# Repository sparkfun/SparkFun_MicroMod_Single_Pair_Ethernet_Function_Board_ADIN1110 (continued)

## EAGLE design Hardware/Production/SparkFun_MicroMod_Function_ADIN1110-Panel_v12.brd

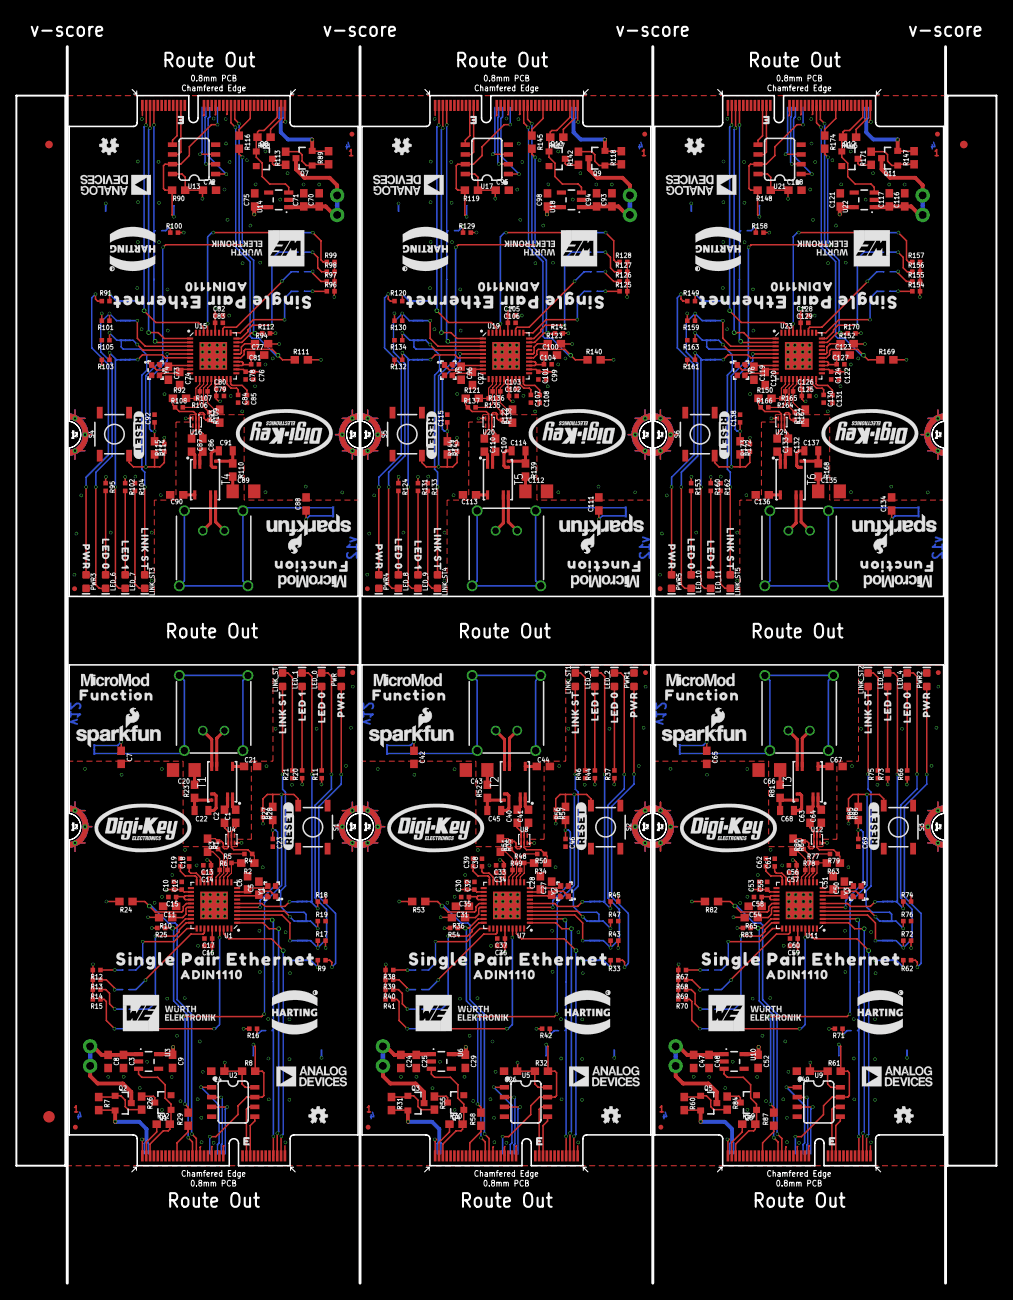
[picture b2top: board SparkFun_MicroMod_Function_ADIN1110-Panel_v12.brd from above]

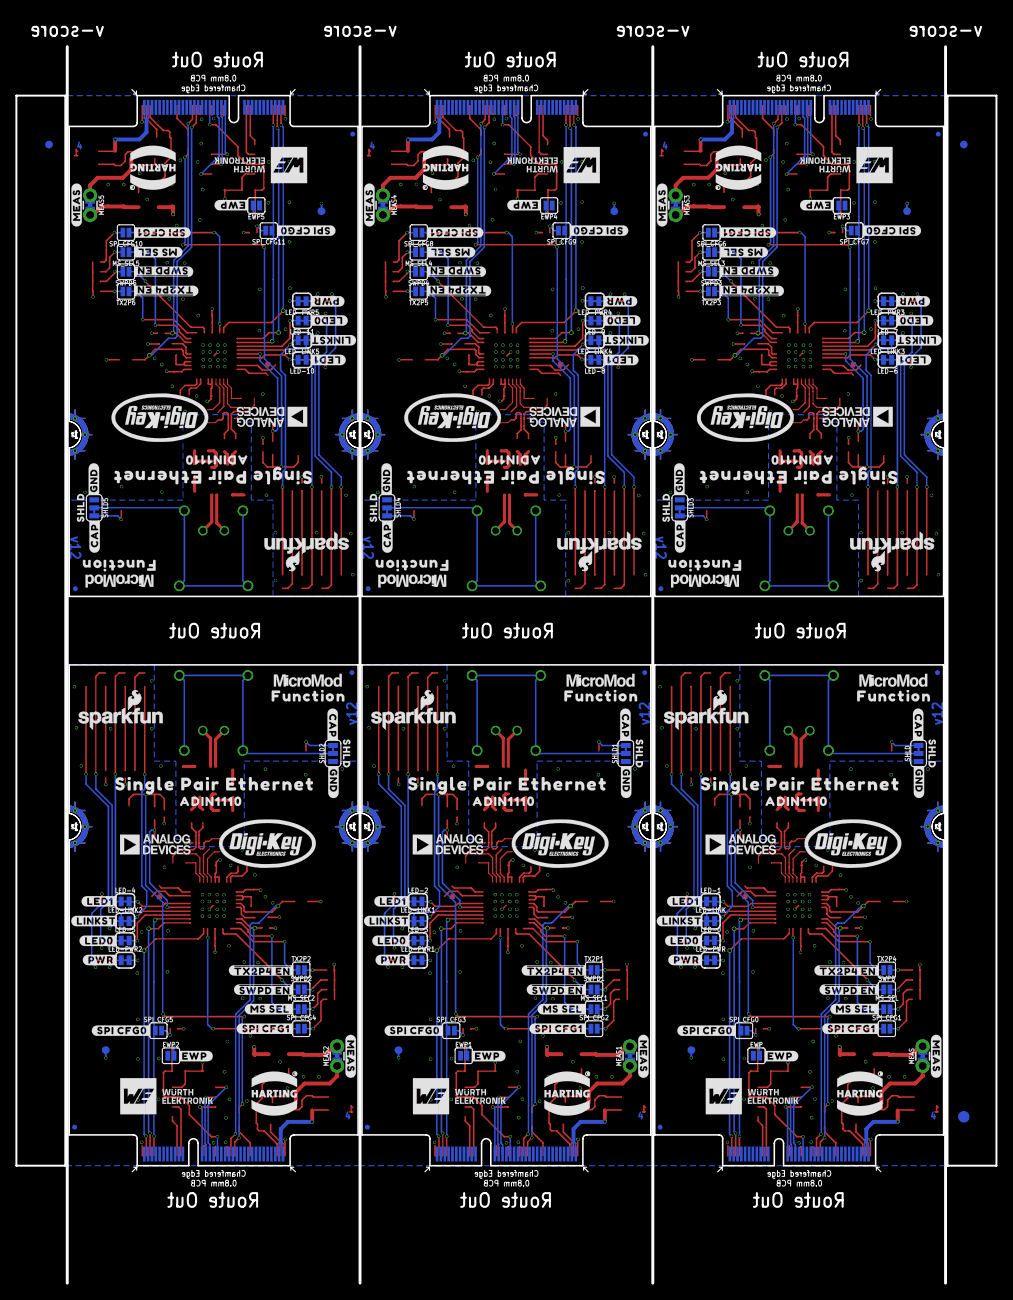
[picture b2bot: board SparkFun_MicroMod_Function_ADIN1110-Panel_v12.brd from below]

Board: 4 copper layers, 127.1 x 164.3 mm, 768 parts (231 on the bottom side), 390 nets.

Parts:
C1, C2, C40, C41, C63, C64, C86, C87, C109, C110, C132, C133: 0.22uF; 0603
C3, C4, C25, C26, C48, C49, C71, C72, C94, C95, C117, C118: 0.1uF; 0603
C5, C6, C27, C28, C50, C51, C73, C74, C96, C97, C119, C120: 10pF; 0603
C7, C42, C65, C88, C111, C134: 3.3nF; 0603
C8, C9, C24, C29, C47, C52, C70, C75, C93, C98, C116, C121: 1.0uF; 0603
C10, C13, C15, C16, C18, C23, C30, C33, C35, C36, C38, C46, C53, C56, C58, C59, C61, C69, C76, C79, C81, C82, C84, C92, C99, C102, C104, C105, C107, C115, C122, C125, C127, C128, C130, C138: 0.1uF; 0402-TIGHT
C11, C31, C54, C77, C100, C123: 0.68uF; 0603
C12, C14, C17, C32, C34, C37, C55, C57, C60, C78, C80, C83, C101, C103, C106, C124, C126, C129: 10nF; 0402-TIGHT
C19, C39, C62, C85, C108, C131: 1.0uF; 0402-TIGHT
C20, C43, C66, C89, C112, C135: 1.0nF/2kV; 1206
C21, C44, C67, C90, C113, C136: 0.1uF/50V; 0603
C22, C45, C68, C91, C114, C137: 470nF/100V; 0805
CIPO, CIPO1, CIPO2, CIPO3, CIPO4, CIPO5: TEST-POINTTP_15TH_THRU; TP_15TH
COPI, COPI1, COPI2, COPI3, COPI4, COPI5: TEST-POINTTP_15TH_THRU; TP_15TH
CS, CS1, CS2, CS3, CS4, CS5: TEST-POINTTP_15TH_THRU; TP_15TH
E$1, E$2, E$3, E$4: FIDUCIAL-1X2
E$5, E$6: FIDUCIAL-1.5X3
EWP, EWP1, EWP2, EWP3, EWP4, EWP5: JUMPER-SMT_2_NO_SILK; SMT-JUMPER_2_NO_SILK
FD1, FD2, FD3, FD4, FD5, FD6, FD7, FD8, FD9, FD10, FD11, FD12, FD13, FD14, FD15, FD16, FD17, FD18, FD19, FD20, FD21, FD22, FD23, FD24: FIDUCIALUFIDUCIAL; FIDUCIAL-MICRO
INT, INT1, INT2, INT3, INT4, INT5: TEST-POINTTP_15TH_THRU; TP_15TH
J1, J4, J6, J8, J10, J12: IP20(RJ50); T1_INDUSTRIAL_JACK_AH_IP20
J2, J3, J5, J7, J9, J11: MICROMOD_FUNCTION_STANDARD; M.2-CARD-E-22_FUNCTION_STANDARD
LED-0, LED-1, LED-2, LED-3, LED-4, LED-5, LED-6, LED-7, LED-8, LED-9, LED-10, LED-11: JUMPER-SMT_2_NC_TRACE_SILK; SMT-JUMPER_2_NC_TRACE_SILK
LED-LINK, LED-LINK1, LED-LINK2, LED-LINK3, LED-LINK4, LED-LINK5: JUMPER-SMT_2_NC_TRACE_SILK; SMT-JUMPER_2_NC_TRACE_SILK
LED-PWR, LED-PWR1, LED-PWR2, LED-PWR3, LED-PWR4, LED-PWR5: JUMPER-SMT_2_NC_TRACE_SILK; SMT-JUMPER_2_NC_TRACE_SILK
LED_0, LED_2, LED_4, LED_6, LED_8, LED_10: Green; LED-0603
LED_1, LED_3, LED_5, LED_7, LED_9, LED_11: Yellow; LED-0603
LINK_ST, LINK_ST1, LINK_ST2, LINK_ST3, LINK_ST4, LINK_ST5: Blue; LED-0603
LOGO1, LOGO4, LOGO6, LOGO8, LOGO10, LOGO12: SFE_LOGO_NAME_FLAME.1_INCH; SFE_LOGO_NAME_FLAME_.1
LOGO2, LOGO3, LOGO5, LOGO7, LOGO9, LOGO11: OSHW-LOGOMINI; OSHW-LOGO-MINI
MEAS, MEAS1, MEAS2, MEAS3, MEAS4, MEAS5: JUMPER-COMBO_2_NC_TRACE; COMBO-JUMPER_2_NC_TRACE
MS_SEL, MS_SEL1, MS_SEL2, MS_SEL3, MS_SEL4, MS_SEL5: SMT-JUMPER_2_NO_SILK
PWR, PWR1, PWR2, PWR3, PWR4, PWR5: Red; LED-0603
Q1, Q4, Q6, Q8, Q10, Q12: 220mA/50V/3.5Ω; SOT23-3
Q2, Q3, Q5, Q7, Q9, Q11: 20V/4.2A/52mΩ/1.4W; SOT23-3
R1, R2, R34, R35, R63, R64, R92, R93, R121, R122, R150, R151: 49.9; 0603
R3, R4, R50, R51, R79, R80, R108, R109, R137, R138, R166, R167: 5.1k; 0402-TIGHT
R5, R6, R48, R49, R77, R78, R106, R107, R135, R136, R164, R165: 10.2k; 0402-TIGHT
R7, R8, R22, R30, R31, R32, R59, R60, R61, R88, R89, R90, R117, R118, R119, R146, R147, R148: 10k; 0603
R9, R11, R20, R21, R33, R37, R44, R46, R62, R66, R73, R75, R91, R95, R102, R104, R120, R124, R131, R133, R149, R153, R160, R162: 1k; 0402-TIGHT
R10, R24, R36, R53, R65, R82, R94, R111, R123, R140, R152, R169: 1.5k; 0603
R12, R13, R14, R15, R16, R17, R18, R19, R25, R38, R39, R40, R41, R42, R43, R45, R47, R54, R67, R68, R69, R70, R71, R72, R74, R76, R83, R96, R97, R98, R99, R100, R101, R103, R105, R112, R125, R126, R127, R128, R129, R130, R132, R134, R141, R154, R155, R156, R157, R158, R159, R161, R163, R170: 4.7k; 0402-TIGHT
R23, R29, R52, R58, R81, R87, R110, R116, R139, R145, R168, R174: 100Ω; 0603
R26, R55, R84, R113, R142, R171: 100; 0603
R27, R56, R85, R114, R143, R172: 4.7k; 0603
R28, R57, R86, R115, R144, R173: 100k; 0402-TIGHT
S1, S2, S3, S4, S5, S6: RESET; TACTILE_SWITCH_SMD_5.2MM
SHLD, SHLD1, SHLD2, SHLD3, SHLD4, SHLD5: SMT-JUMPER_3_1-NC_TRACE_SILK
SPI, SPI1, SPI2, SPI3, SPI4, SPI5: TEST-POINTTP_15TH_THRU; TP_15TH
SPI_CFG0, SPI_CFG1, SPI_CFG2, SPI_CFG3, SPI_CFG4, SPI_CFG5, SPI_CFG6, SPI_CFG7, SPI_CFG8, SPI_CFG9, SPI_CFG10, SPI_CFG11: SMT-JUMPER_2_NO_SILK
SWPD, SWPD1, SWPD2, SWPD3, SWPD4, SWPD5: SMT-JUMPER_2_NO_SILK
T1, T2, T3, T4, T5, T6: WE-STST; WE_STST_TRANSFORMER_1:1_SMD_3.2X4.7MM_74930030
TP1, TP2, TP3, TP4, TP5, TP6: TEST-POINT3X4; PAD.03X.04
TX2P1, TX2P2, TX2P3, TX2P4, TX2P5, TX2P6: SMT-JUMPER_2_NO_SILK
U1, U7, U11, U15, U19, U23: ADIN1110; LFCSP-40
U2, U5, U9, U13, U17, U21: EEPROM; SO08
U3, U6, U10, U14, U18, U22: 3.3V; SOT23-5
U4, U8, U12, U16, U20, U24: WE-TVS; WE_TVS_1.0X1.2MM
U$1, U$42, U$79, U$115, U$151, U$187: #RESET#0
U$2, U$71, U$107, U$143, U$179, U$215: HARTING_LOGO; HARTING_LOGO_9MM
U$3, U$36, U$37, U$63, U$73, U$74, U$109, U$110, U$145, U$146, U$181, U$182: MICROMOD_LOGO_.35
U$4, U$21, U$41, U$47, U$78, U$84, U$114, U$120, U$150, U$156, U$186, U$192: ADIN11100
U$5, U$69, U$105, U$141, U$177, U$213: DIGIKEY_LOGO
U$6, U$55, U$92, U$128, U$164, U$200: #PWR#19
U$7, U$39, U$76, U$112, U$148, U$184: PWR0
U$8, U$43, U$80, U$116, U$152, U$188: SHLD11
U$9, U$54, U$91, U$127, U$163, U$199: #EWP#18
U$10, U$56, U$93, U$129, U$165, U$201: #LED0#20
U$11, U$52, U$89, U$125, U$161, U$197: #GND#16
U$12, U$53, U$90, U$126, U$162, U$198: #CAP#17
U$13, U$59, U$96, U$132, U$168, U$204: ##TX2P4_EN##4
U$14, U$44, U$81, U$117, U$153, U$189: #SPI_CFG1#0
U$15, U$45, U$82, U$118, U$154, U$190: #MS_SEL#2
U$16, U$46, U$83, U$119, U$155, U$191: #SPI_CFG0#0
U$17, U$18, U$61, U$62, U$98, U$99, U$134, U$135, U$170, U$171, U$206, U$207: SINGLE_PAIR_ETHERNET0
U$19, U$72, U$108, U$144, U$180, U$216: WURTH_LOGO; WURTH_LOGO_9MM
U$20, U$64, U$100, U$136, U$172, U$208: ANALOG_DEVICE_LOGO_9MM
U$22, U$60, U$97, U$133, U$169, U$205: ##SWPD_EN##4
U$23, U$49, U$86, U$122, U$158, U$194: LED_03
U$24, U$26, U$40, U$48, U$77, U$85, U$113, U$121, U$149, U$157, U$185, U$193: FUNCTION0
U$25, U$50, U$87, U$123, U$159, U$195: LED_14
U$27, U$51, U$88, U$124, U$160, U$196: LINK_ST15
U$28, U$38, U$75, U$111, U$147, U$183: #MEAS#3
U$29, U$57, U$94, U$130, U$166, U$202: #LED1#21
U$30, U$65, U$101, U$137, U$173, U$209: HARTING_LOGO_9MM
U$31, U$58, U$95, U$131, U$167, U$203: #LINKST#2
U$32, U$66, U$102, U$138, U$174, U$210: WURTH_LOGO_9MM
U$33, U$70, U$106, U$142, U$178, U$214: ANALOG_DEVICES_LOGO; ANALOG_DEVICE_LOGO_9MM
U$34, U$67, U$103, U$139, U$175, U$211: DIGIKEY_LOGO
U$35, U$68, U$104, U$140, U$176, U$212: SFE_LOGO_NAME_FLAME_.1
Y1, Y2, Y3, Y4, Y5, Y6: 25MHz; CRYSTAL-SMD-2.0X1.6MM-WE

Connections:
1.1V: C11.1, C15.1, U1.23, U1.24
1.1V1: C31.1, C35.1, U7.23, U7.24
1.1V2: C54.1, C58.1, U11.23, U11.24
1.1V3: C77.1, C81.1, U15.23, U15.24
1.1V4: C100.1, C104.1, U19.23, U19.24
1.1V5: C123.1, C127.1, U23.23, U23.24
3.3V: C4.1, C9.1, C10.1, C12.1, C13.1, C14.1, C16.1, C17.1, LED-PWR.2, R8.1, R10.2, R11.1, R12.2, R13.2, R14.2, R15.2, R16.2, R17.2, R18.2, R20.1, R24.2, R25.2, R28.2, TP1.1, U1.16, U1.17, U1.22, U1.35, U2.8, U3.5
3.3V1: C26.1, C29.1, C30.1, C32.1, C33.1, C34.1, C36.1, C37.1, LED-PWR1.2, R32.1, R36.2, R37.1, R38.2, R39.2, R40.2, R41.2, R42.2, R43.2, R44.1, R45.2, R53.2, R54.2, R57.2, TP2.1, U5.8, U6.5, U7.16, U7.17, U7.22, U7.35
3.3V2: C49.1, C52.1, C53.1, C55.1, C56.1, C57.1, C59.1, C60.1, LED-PWR2.2, R61.1, R65.2, R66.1, R67.2, R68.2, R69.2, R70.2, R71.2, R72.2, R73.1, R74.2, R82.2, R83.2, R86.2, TP3.1, U9.8, U10.5, U11.16, U11.17, U11.22, U11.35
3.3V3: C72.1, C75.1, C76.1, C78.1, C79.1, C80.1, C82.1, C83.1, LED-PWR3.2, R90.1, R94.2, R95.1, R96.2, R97.2, R98.2, R99.2, R100.2, R101.2, R102.1, R103.2, R111.2, R112.2, R115.2, TP4.1, U13.8, U14.5, U15.16, U15.17, U15.22, U15.35
3.3V4: C95.1, C98.1, C99.1, C101.1, C102.1, C103.1, C105.1, C106.1, LED-PWR4.2, R119.1, R123.2, R124.1, R125.2, R126.2, R127.2, R128.2, R129.2, R130.2, R131.1, R132.2, R140.2, R141.2, R144.2, TP5.1, U17.8, U18.5, U19.16, U19.17, U19.22, U19.35
3.3V5: C118.1, C121.1, C122.1, C124.1, C125.1, C126.1, C128.1, C129.1, LED-PWR5.2, R148.1, R152.2, R153.1, R154.2, R155.2, R156.2, R157.2, R158.2, R159.2, R160.1, R161.2, R169.2, R170.2, R173.2, TP6.1, U21.8, U22.5, U23.16, U23.17, U23.22, U23.35
3.3V_IN: J2.73, R22.1
3.3V_IN1: J3.73, R30.1
3.3V_IN2: J5.73, R59.1
3.3V_IN3: J7.73, R88.1
3.3V_IN4: J9.73, R117.1
3.3V_IN5: J11.73, R146.1
!CS!: CS.1, J2.49, R25.1, U1.29
!CS!1: CS1.1, J3.49, R54.1, U7.29
!CS!2: CS2.1, J5.49, R83.1, U11.29
!CS!3: CS3.1, J7.49, R112.1, U15.29
!CS!4: CS4.1, J9.49, R141.1, U19.29
!CS!5: CS5.1, J11.49, R170.1, U23.29
!INT!: INT.1, J2.47, R24.1, U1.25
!INT!1: INT1.1, J3.47, R53.1, U7.25
!INT!2: INT2.1, J5.47, R82.1, U11.25
!INT!3: INT3.1, J7.47, R111.1, U15.25
!INT!4: INT4.1, J9.47, R140.1, U19.25
!INT!5: INT5.1, J11.47, R169.1, U23.25
!RESET!: J2.57, R29.1
!RESET!1: J3.57, R58.1
!RESET!2: J5.57, R87.1
!RESET!3: J7.57, R116.1
!RESET!4: J9.57, R145.1
!RESET!5: J11.57, R174.1
!SWPD_EN!: SWPD.1, U1.33
!SWPD_EN!1: SWPD1.1, U7.33
!SWPD_EN!2: SWPD2.1, U11.33
!SWPD_EN!3: SWPD3.1, U15.33
!SWPD_EN!4: SWPD4.1, U19.33
!SWPD_EN!5: SWPD5.1, U23.33
!TX2P4_EN!: TX2P4.1, U1.31
!TX2P4_EN!1: TX2P1.1, U7.31
!TX2P4_EN!2: TX2P2.1, U11.31
!TX2P4_EN!3: TX2P3.1, U15.31
!TX2P4_EN!4: TX2P5.1, U19.31
!TX2P4_EN!5: TX2P6.1, U23.31
A0: J2.36, U2.1
A1: J2.34, U2.2
A2: J2.32, U2.3
A3: J3.36, U5.1
A4: J3.32, U5.3
A5: J3.34, U5.2
A6: J5.36, U9.1
A7: J5.32, U9.3
A8: J5.34, U9.2
A9: J7.36, U13.1
A10: J7.32, U13.3
A11: J7.34, U13.2
A12: J9.36, U17.1
A13: J9.32, U17.3
A14: J9.34, U17.2
A15: J11.36, U21.1
A16: J11.32, U21.3
A17: J11.34, U21.2
DA+: J1.1, T1.7
DA+1: J4.1, T2.7
DA+2: J6.1, T3.7
DA+3: J8.1, T4.7
DA+4: J10.1, T5.7
DA+5: J12.1, T6.7
DA-: J1.2, T1.6
DA-1: J4.2, T2.6
DA-2: J6.2, T3.6
DA-3: J8.2, T4.6
DA-4: J10.2, T5.6
DA-5: J12.2, T6.6
EWP: EWP.2, J2.40, R8.2, U2.7
EWP1: EWP1.2, J3.40, R32.2, U5.7
EWP2: EWP2.2, J5.40, R61.2, U9.7
EWP3: EWP3.2, J7.40, R90.2, U13.7
EWP4: EWP4.2, J9.40, R119.2, U17.7
EWP5: EWP5.2, J11.40, R148.2, U21.7
GND: C3.2, C4.2, C5.2, C6.2, C7.2, C8.2, C9.2, C10.2, C11.2, C12.2, C13.2, C14.2, C15.2, C16.2, C17.2, C18.2, C19.2, C20.2, C21.2, C23.2, EWP.1, J2.1, J2.2, J2.8, J2.33, J2.39, J2.45, J2.75, J2.GND1, J2.GND2, J2.GND3, J2.GND4, J2.GND5, J2.GND6, PWR.C, Q1.2, R19.2, R21.1, S1.1, SHLD.1, U1.EP, U2.4, U3.2, U4.3, Y1.2, Y1.4
GND1: C24.2, C25.2, C26.2, C27.2, C28.2, C29.2, C30.2, C31.2, C32.2, C33.2, C34.2, C35.2, C36.2, C37.2, C38.2, C39.2, C42.2, C43.2, C44.2, C46.2, EWP1.1, J3.1, J3.2, J3.8, J3.33, J3.39, J3.45, J3.75, J3.GND1, J3.GND2, J3.GND3, J3.GND4, J3.GND5, J3.GND6, PWR1.C, Q4.2, R46.1, R47.2, S2.1, SHLD1.1, U5.4, U6.2, U7.EP, U8.3, Y2.2, Y2.4
GND2: C47.2, C48.2, C49.2, C50.2, C51.2, C52.2, C53.2, C54.2, C55.2, C56.2, C57.2, C58.2, C59.2, C60.2, C61.2, C62.2, C65.2, C66.2, C67.2, C69.2, EWP2.1, J5.1, J5.2, J5.8, J5.33, J5.39, J5.45, J5.75, J5.GND1, J5.GND2, J5.GND3, J5.GND4, J5.GND5, J5.GND6, PWR2.C, Q6.2, R75.1, R76.2, S3.1, SHLD2.1, U9.4, U10.2, U11.EP, U12.3, Y3.2, Y3.4
GND3: C70.2, C71.2, C72.2, C73.2, C74.2, C75.2, C76.2, C77.2, C78.2, C79.2, C80.2, C81.2, C82.2, C83.2, C84.2, C85.2, C88.2, C89.2, C90.2, C92.2, EWP3.1, J7.1, J7.2, J7.8, J7.33, J7.39, J7.45, J7.75, J7.GND1, J7.GND2, J7.GND3, J7.GND4, J7.GND5, J7.GND6, PWR3.C, Q8.2, R104.1, R105.2, S4.1, SHLD3.1, U13.4, U14.2, U15.EP, U16.3, Y4.2, Y4.4
GND4: C93.2, C94.2, C95.2, C96.2, C97.2, C98.2, C99.2, C100.2, C101.2, C102.2, C103.2, C104.2, C105.2, C106.2, C107.2, C108.2, C111.2, C112.2, C113.2, C115.2, EWP4.1, J9.1, J9.2, J9.8, J9.33, J9.39, J9.45, J9.75, J9.GND1, J9.GND2, J9.GND3, J9.GND4, J9.GND5, J9.GND6, PWR4.C, Q10.2, R133.1, R134.2, S5.1, SHLD4.1, U17.4, U18.2, U19.EP, U20.3, Y5.2, Y5.4
GND5: C116.2, C117.2, C118.2, C119.2, C120.2, C121.2, C122.2, C123.2, C124.2, C125.2, C126.2, C127.2, C128.2, C129.2, C130.2, C131.2, C134.2, C135.2, C136.2, C138.2, EWP5.1, J11.1, J11.2, J11.8, J11.33, J11.39, J11.45, J11.75, J11.GND1, J11.GND2, J11.GND3, J11.GND4, J11.GND5, J11.GND6, PWR5.C, Q12.2, R162.1, R163.2, S6.1, SHLD5.1, U21.4, U22.2, U23.EP, U24.3, Y6.2, Y6.4
I2C_SCL: J2.21, U2.6
I2C_SCL1: J3.21, U5.6
I2C_SCL2: J5.21, U9.6
I2C_SCL3: J7.21, U13.6
I2C_SCL4: J9.21, U17.6
I2C_SCL5: J11.21, U21.6
I2C_SDA: J2.19, U2.5
I2C_SDA1: J3.19, U5.5
I2C_SDA2: J5.19, U9.5
I2C_SDA3: J7.19, U13.5
I2C_SDA4: J9.19, U17.5
I2C_SDA5: J11.19, U21.5
LED_0: LED-0.2, U1.3
LED_1: LED-1.2, U1.6
LED_2: LED-2.2, U7.6
LED_3: LED-3.2, U7.3
LED_4: LED-4.2, U11.6
LED_5: LED-5.2, U11.3
LED_6: LED-6.2, U15.6
LED_7: LED-7.2, U15.3
LED_8: LED-8.2, U19.6
LED_9: LED-9.2, U19.3
LED_10: LED-10.2, U23.6
LED_11: LED-11.2, U23.3
LINK_ST: LED-LINK.2, U1.4
LINK_ST1: LED-LINK1.2, U7.4
LINK_ST2: LED-LINK2.2, U11.4
LINK_ST3: LED-LINK3.2, U15.4
LINK_ST4: LED-LINK4.2, U19.4
LINK_ST5: LED-LINK5.2, U23.4
MS_SEL: MS_SEL.1, U1.30
MS_SEL1: MS_SEL1.1, U7.30
MS_SEL2: MS_SEL2.1, U11.30
MS_SEL3: MS_SEL3.1, U15.30
MS_SEL4: MS_SEL4.1, U19.30
MS_SEL5: MS_SEL5.1, U23.30
unnamed: MEAS.1, MEAS.3, Q2.3
unnamed: C3.1, C8.1, MEAS.2, MEAS.4, U3.1
unnamed: C21.1, T1.5
unnamed: C22.1, T1.4
unnamed: LED-LINK.1, LINK_ST.A, R19.1
unnamed: LED-1.1, LED_1.C, R18.1
unnamed: C22.2, R23.1, T1.3
unnamed: C20.1, R23.2
unnamed: LED-0.1, LED_0.C, R17.1
unnamed: Q1.3, R26.1
unnamed: Q2.1, R7.1, R26.2
unnamed: C5.1, U1.8, Y1.1
unnamed: C23.1, R27.1, U1.5
unnamed: C6.1, U1.9, Y1.3
unnamed: R27.2, R28.1, R29.2, S1.3
unnamed: C24.1, C25.1, MEAS1.2, MEAS1.4, U6.1
unnamed: MEAS1.1, MEAS1.3, Q3.3
unnamed: R10.1, U1.26
unnamed: LED-PWR.1, R9.2
unnamed: PWR.A, R9.1
unnamed: C18.1, U1.19
unnamed: C19.1, U1.20
unnamed: LED_0.A, R11.2
unnamed: C1.1, R2.1, R4.1, U4.2, U4.5
unnamed: MS_SEL.2, R14.1
unnamed: R13.1, SWPD.2
unnamed: R12.1, TX2P4.2
unnamed: R16.1, SPI_CFG0.2
unnamed: R15.1, SPI_CFG1.2
unnamed: LED_1.A, R20.2
unnamed: C2.1, R1.1, R3.2, U4.1, U4.6
unnamed: C1.2, T1.1
unnamed: LINK_ST.C, R21.2
unnamed: C2.2, T1.2
unnamed: R4.2, R6.2, U1.13
unnamed: R3.1, R5.1, U1.14
unnamed: R1.2, R6.1, U1.15
unnamed: R2.2, R5.2, U1.12
unnamed: Q3.1, R31.1, R55.2
unnamed: LED-PWR1.1, R33.2
unnamed: C7.1, SHLD.3
unnamed: PWR1.A, R33.1
unnamed: J1.S1, J1.S2, J1.S3, J1.S4, SHLD.2
unnamed: C27.1, U7.8, Y2.1
unnamed: C28.1, U7.9, Y2.3
unnamed: R56.2, R57.1, R58.2, S2.3
unnamed: R36.1, U7.26
unnamed: C38.1, U7.19
unnamed: C39.1, U7.20
unnamed: MS_SEL1.2, R40.1
unnamed: R39.1, SWPD1.2
unnamed: R38.1, TX2P1.2
unnamed: R42.1, SPI_CFG3.2
unnamed: R41.1, SPI_CFG2.2
unnamed: LED_2.A, R37.2
unnamed: LED_3.A, R44.2
unnamed: LINK_ST1.C, R46.2
unnamed: C41.1, R34.1, R50.1, U8.2, U8.5
unnamed: C40.1, R35.1, R51.2, U8.1, U8.6
unnamed: R49.2, R50.2, U7.13
unnamed: R48.1, R51.1, U7.14
unnamed: R35.2, R49.1, U7.15
unnamed: R34.2, R48.2, U7.12
unnamed: C41.2, T2.1
unnamed: C40.2, T2.2
unnamed: C42.1, SHLD1.3
unnamed: J4.S1, J4.S2, J4.S3, J4.S4, SHLD1.2
unnamed: C44.1, T2.5
unnamed: C45.1, T2.4
unnamed: C45.2, R52.1, T2.3
unnamed: C43.1, R52.2
unnamed: LED-LINK1.1, LINK_ST1.A, R47.1
unnamed: LED-2.1, LED_3.C, R45.1
unnamed: LED-3.1, LED_2.C, R43.1
unnamed: Q4.3, R55.1
unnamed: C46.1, R56.1, U7.5
unnamed: C47.1, C48.1, MEAS2.2, MEAS2.4, U10.1
unnamed: MEAS2.1, MEAS2.3, Q5.3
unnamed: Q5.1, R60.1, R84.2
unnamed: LED-PWR2.1, R62.2
unnamed: PWR2.A, R62.1
unnamed: C50.1, U11.8, Y3.1
unnamed: C51.1, U11.9, Y3.3
unnamed: R85.2, R86.1, R87.2, S3.3
unnamed: R65.1, U11.26
unnamed: C61.1, U11.19
unnamed: C62.1, U11.20
unnamed: MS_SEL2.2, R69.1
unnamed: R68.1, SWPD2.2
unnamed: R67.1, TX2P2.2
unnamed: R71.1, SPI_CFG5.2
unnamed: R70.1, SPI_CFG4.2
unnamed: LED_4.A, R66.2
unnamed: LED_5.A, R73.2
unnamed: LINK_ST2.C, R75.2
unnamed: C64.1, R63.1, R79.1, U12.2, U12.5
unnamed: C63.1, R64.1, R80.2, U12.1, U12.6
unnamed: R78.2, R79.2, U11.13
unnamed: R77.1, R80.1, U11.14
unnamed: R64.2, R78.1, U11.15
unnamed: R63.2, R77.2, U11.12
unnamed: C64.2, T3.1
unnamed: C63.2, T3.2
unnamed: C65.1, SHLD2.3
unnamed: J6.S1, J6.S2, J6.S3, J6.S4, SHLD2.2
unnamed: C67.1, T3.5
unnamed: C68.1, T3.4
unnamed: C68.2, R81.1, T3.3
unnamed: C66.1, R81.2
unnamed: LED-LINK2.1, LINK_ST2.A, R76.1
unnamed: LED-4.1, LED_5.C, R74.1
unnamed: LED-5.1, LED_4.C, R72.1
unnamed: Q6.3, R84.1
unnamed: C69.1, R85.1, U11.5
unnamed: C70.1, C71.1, MEAS3.2, MEAS3.4, U14.1
unnamed: MEAS3.1, MEAS3.3, Q7.3
unnamed: Q7.1, R89.1, R113.2
unnamed: LED-PWR3.1, R91.2
unnamed: PWR3.A, R91.1
unnamed: C73.1, U15.8, Y4.1
unnamed: C74.1, U15.9, Y4.3
unnamed: R114.2, R115.1, R116.2, S4.3
unnamed: R94.1, U15.26
unnamed: C84.1, U15.19
unnamed: C85.1, U15.20
unnamed: MS_SEL3.2, R98.1
unnamed: R97.1, SWPD3.2
unnamed: R96.1, TX2P3.2
unnamed: R100.1, SPI_CFG7.2
unnamed: R99.1, SPI_CFG6.2
unnamed: LED_6.A, R95.2
unnamed: LED_7.A, R102.2
unnamed: LINK_ST3.C, R104.2
unnamed: C87.1, R92.1, R108.1, U16.2, U16.5
unnamed: C86.1, R93.1, R109.2, U16.1, U16.6
unnamed: R107.2, R108.2, U15.13
unnamed: R106.1, R109.1, U15.14
unnamed: R93.2, R107.1, U15.15
unnamed: R92.2, R106.2, U15.12
unnamed: C87.2, T4.1
unnamed: C86.2, T4.2
unnamed: C88.1, SHLD3.3
unnamed: J8.S1, J8.S2, J8.S3, J8.S4, SHLD3.2
unnamed: C90.1, T4.5
unnamed: C91.1, T4.4
unnamed: C91.2, R110.1, T4.3
unnamed: C89.1, R110.2
unnamed: LED-LINK3.1, LINK_ST3.A, R105.1
unnamed: LED-6.1, LED_7.C, R103.1
unnamed: LED-7.1, LED_6.C, R101.1
unnamed: Q8.3, R113.1
unnamed: C92.1, R114.1, U15.5
unnamed: C93.1, C94.1, MEAS4.2, MEAS4.4, U18.1
unnamed: MEAS4.1, MEAS4.3, Q9.3
unnamed: Q9.1, R118.1, R142.2
unnamed: LED-PWR4.1, R120.2
unnamed: PWR4.A, R120.1
unnamed: C96.1, U19.8, Y5.1
unnamed: C97.1, U19.9, Y5.3
unnamed: R143.2, R144.1, R145.2, S5.3
unnamed: R123.1, U19.26
unnamed: C107.1, U19.19
unnamed: C108.1, U19.20
unnamed: MS_SEL4.2, R127.1
unnamed: R126.1, SWPD4.2
unnamed: R125.1, TX2P5.2
unnamed: R129.1, SPI_CFG9.2
unnamed: R128.1, SPI_CFG8.2
unnamed: LED_8.A, R124.2
unnamed: LED_9.A, R131.2
unnamed: LINK_ST4.C, R133.2
unnamed: C110.1, R121.1, R137.1, U20.2, U20.5
unnamed: C109.1, R122.1, R138.2, U20.1, U20.6
unnamed: R136.2, R137.2, U19.13
unnamed: R135.1, R138.1, U19.14
unnamed: R122.2, R136.1, U19.15
unnamed: R121.2, R135.2, U19.12
unnamed: C110.2, T5.1
unnamed: C109.2, T5.2
unnamed: C111.1, SHLD4.3
unnamed: J10.S1, J10.S2, J10.S3, J10.S4, SHLD4.2
unnamed: C113.1, T5.5
unnamed: C114.1, T5.4
unnamed: C114.2, R139.1, T5.3
unnamed: C112.1, R139.2
unnamed: LED-LINK4.1, LINK_ST4.A, R134.1
unnamed: LED-8.1, LED_9.C, R132.1
unnamed: LED-9.1, LED_8.C, R130.1
unnamed: Q10.3, R142.1
unnamed: C115.1, R143.1, U19.5
unnamed: C116.1, C117.1, MEAS5.2, MEAS5.4, U22.1
unnamed: MEAS5.1, MEAS5.3, Q11.3
unnamed: Q11.1, R147.1, R171.2
unnamed: LED-PWR5.1, R149.2
unnamed: PWR5.A, R149.1
unnamed: C119.1, U23.8, Y6.1
unnamed: C120.1, U23.9, Y6.3
unnamed: R172.2, R173.1, R174.2, S6.3
unnamed: R152.1, U23.26
unnamed: C130.1, U23.19
unnamed: C131.1, U23.20
unnamed: MS_SEL5.2, R156.1
unnamed: R155.1, SWPD5.2
unnamed: R154.1, TX2P6.2
unnamed: R158.1, SPI_CFG11.2
unnamed: R157.1, SPI_CFG10.2
unnamed: LED_10.A, R153.2
unnamed: LED_11.A, R160.2
unnamed: LINK_ST5.C, R162.2
unnamed: C133.1, R150.1, R166.1, U24.2, U24.5
unnamed: C132.1, R151.1, R167.2, U24.1, U24.6
unnamed: R165.2, R166.2, U23.13
unnamed: R164.1, R167.1, U23.14
unnamed: R151.2, R165.1, U23.15
unnamed: R150.2, R164.2, U23.12
unnamed: C133.2, T6.1
unnamed: C132.2, T6.2
unnamed: C134.1, SHLD5.3
unnamed: J12.S1, J12.S2, J12.S3, J12.S4, SHLD5.2
unnamed: C136.1, T6.5
unnamed: C137.1, T6.4
unnamed: C137.2, R168.1, T6.3
unnamed: C135.1, R168.2
unnamed: LED-LINK5.1, LINK_ST5.A, R163.1
unnamed: LED-10.1, LED_11.C, R161.1
unnamed: LED-11.1, LED_10.C, R159.1
unnamed: Q12.3, R171.1
unnamed: C138.1, R172.1, U23.5
PWR_EN: J2.71, Q1.1, R22.2, U3.3
PWR_EN1: J3.71, Q4.1, R30.2, U6.3
PWR_EN2: J5.71, Q6.1, R59.2, U10.3
PWR_EN3: J7.71, Q8.1, R88.2, U14.3
PWR_EN4: J9.71, Q10.1, R117.2, U18.3
PWR_EN5: J11.71, Q12.1, R146.2, U22.3
SPI_CFG1: SPI_CFG1.1, U1.37
SPI_CFG2: SPI_CFG2.1, U7.37
SPI_CFG3: SPI_CFG4.1, U11.37
SPI_CFG4: SPI_CFG6.1, U15.37
SPI_CFG5: SPI_CFG8.1, U19.37
SPI_CFG6: SPI_CFG10.1, U23.37
SPI_PICO: COPI.1, J2.5, U1.1
SPI_PICO1: COPI1.1, J3.5, U7.1
SPI_PICO2: COPI2.1, J5.5, U11.1
SPI_PICO3: COPI3.1, J7.5, U15.1
SPI_PICO4: COPI4.1, J9.5, U19.1
SPI_PICO5: COPI5.1, J11.5, U23.1
SPI_POCI/SPI_CFG0: CIPO.1, J2.7, SPI_CFG0.1, U1.2
SPI_POCI/SPI_CFG1: CIPO1.1, J3.7, SPI_CFG3.1, U7.2
SPI_POCI/SPI_CFG2: CIPO2.1, J5.7, SPI_CFG5.1, U11.2
SPI_POCI/SPI_CFG3: CIPO3.1, J7.7, SPI_CFG7.1, U15.2
SPI_POCI/SPI_CFG4: CIPO4.1, J9.7, SPI_CFG9.1, U19.2
SPI_POCI/SPI_CFG5: CIPO5.1, J11.7, SPI_CFG11.1, U23.2
SPI_SCK: J2.3, SPI.1, U1.38
SPI_SCK1: J3.3, SPI1.1, U7.38
SPI_SCK2: J5.3, SPI2.1, U11.38
SPI_SCK3: J7.3, SPI3.1, U15.38
SPI_SCK4: J9.3, SPI4.1, U19.38
SPI_SCK5: J11.3, SPI5.1, U23.38
VCC_IN: J2.72, J2.74, Q2.2, R7.2
VCC_IN1: J3.72, J3.74, Q3.2, R31.2
VCC_IN2: J5.72, J5.74, Q5.2, R60.2
VCC_IN3: J7.72, J7.74, Q7.2, R89.2
VCC_IN4: J9.72, J9.74, Q9.2, R118.2
VCC_IN5: J11.72, J11.74, Q11.2, R147.2

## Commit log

2021-11-08 datasheet
2021-11-11 IC in private library to start
2021-11-22 SCH import and some preliminary part placement
2021-11-29 HARTING T1 connector added and layout work
2021-11-30 sch cleanup
2021-12-01 some checklist catches - sch cleanup
2021-12-01 new parts datasheets
2021-12-03 Added transformer isolation and TVS diode array
2021-12-13 Prototype Design Review Changes
    -Moved LEDs to upper edge.
    -Backed off GND pour from connector for better isolation
    -added jumpers to disable each LED if desired
    -Schematic symbols cleanup and note corrections
    -moved 3.3V testpoint to match other Ethernet MM board.
    -tightened FP drills on T1 connector
2021-12-16 checklist catches
    -added CS and INT pulllups
    -nudged vias to avoid silk
    -added 1/2/3/4 text objects to help indicate 4 layers
    -added suggested Selective Solder path on layer 48
    -adjusted tnames for better assembly sheet
    -added measures
2021-12-16 connected RESET to MM GPIO (F5)
    -needed for testing, but also could be useful for the user to perform a hard reset on the ANIN1110 from GPIO controlled on their MM main board.
2021-12-17 Final tweaks before ordering protos
    -pulled GND back out to LEDS
    -reverted back to T1 connector max tolerance drill size
    -added connector width to measures
2021-12-17 Prototype Panel
2022-01-06 Wurth Electronik caps
2022-01-07 LEDs and Xtal swapped out for Wurth Electronic Parts
    Also bumped version to v10, because the WE xtal has GND pads, and new package has polarity dot.
2022-01-13 Switched C21 from 0402 to 0603 package
    Due to sourcing issues.
2022-01-14 Add Prod_IDs to T1 connectors
    updated single and panel brd files
2022-01-17 R3, R4, R5, R6 to in-house PROD_IDs
    Note, these values are very slightly different than the ones in the DS sch.
2022-01-17 Update PROD_IDs for 10ohm and 4.7ohm resistors on production panel
2022-02-07 TVS diode placement and more
    -Moved TVS diodes to "IC" side of DA-/DA+ DC coupling caps
    -Added debounce to reset button
    -Routed through pads 5 and 6 on TVS diode package.
    -Added R29 to avoid damaging GPIO if set to output low and button pressed
    -Added R26 to mosfet gate control line to avoid potential overvoltage/ringing
    -Re-arranged caps so smalled value decoupling caps are closest to pins on IC.
2022-02-08 470pF cap to 0805 with new PROD_ID
    -new 470nF cap had to bump up to 0805 for the 100V rating in that value
    -Voltage specs in part values
2022-02-24 SPI test points and moved config jumpers
    -moved bottom config jumpers to avoid reflections on CIPO
    -added SPI test points
2022-02-25 Renaming CIPO/COPI to POCI/PICO
2022-02-25 Adjusted inner layer to match top/bottom copper
    -Now the inner layers "back away" from the connector and transformer exactly the same as the top and bottom layers.
2022-03-03 Production panel and gerbers v10d
2022-03-11 PROD_ID for 0.68uF 0603 Cap (C11)
2022-03-11 added PROD_IDs to all 0.68uF caps on panel file
2022-03-30 Silk updated to "Single Pair Ethernet"
    -updated product name silk
    -bumped version to v11 in brd and sch
2022-03-31 reduced width by 0.01" on each side
    -This will help avoid overlap issues when plugging in two of these boards into the main-double.
2022-04-01 Panel for v11
2022-04-20 R27 changed to 4.7K
    -updated prod_id and values on boat single and panel files.
2022-04-21 Updated Measures to match actual new width
2022-05-03 Update README.md
    Updating README with relevant links and information.
2022-06-23 v12 - partner logos added
2022-06-27 Removed v11 panel and added v12 panel
